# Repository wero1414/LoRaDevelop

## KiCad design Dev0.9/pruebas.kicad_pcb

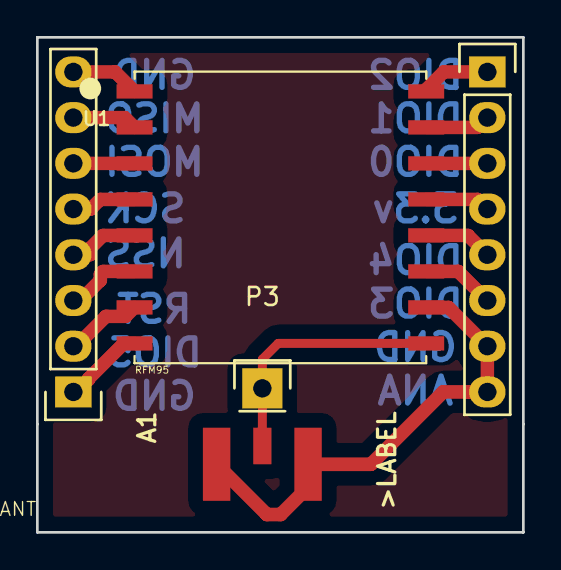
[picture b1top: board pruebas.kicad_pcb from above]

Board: 2 copper layers, 27.0 x 27.5 mm, 5 parts (0 on the bottom side), 16 nets.

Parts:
A1: ANT; SMA_Conn_Ant
P1, P2: CONN_01X08; Socket_Strip_Straight_1x08
P3: CONN_01X01; Pin_Header_Straight_1x01
U1: RFM95; RFM

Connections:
unnamed: A1.1, A1.3, P2.7, P2.8, U1.15
unnamed: A1.2, P3.1, U1.16
unnamed: P1.1, U1.8
unnamed: P1.2, U1.7
unnamed: P1.3, U1.6
unnamed: P1.4, U1.5
unnamed: P1.5, U1.4
unnamed: P1.6, U1.3
unnamed: P1.7, U1.2
unnamed: P1.8, U1.1
unnamed: P2.1, U1.9
unnamed: P2.2, U1.10
unnamed: P2.3, U1.11
unnamed: P2.4, U1.12
unnamed: P2.5, U1.13
unnamed: P2.6, U1.14

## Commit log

2016-06-25 First version of library for KiCad of RFM95 and development board 0.9v
2016-07-24 Added working program to get communicate 2 LoRa with arduino
